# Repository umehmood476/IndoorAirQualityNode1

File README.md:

# IndoorAirQualityNode1
Indoor Air Quality Node 1

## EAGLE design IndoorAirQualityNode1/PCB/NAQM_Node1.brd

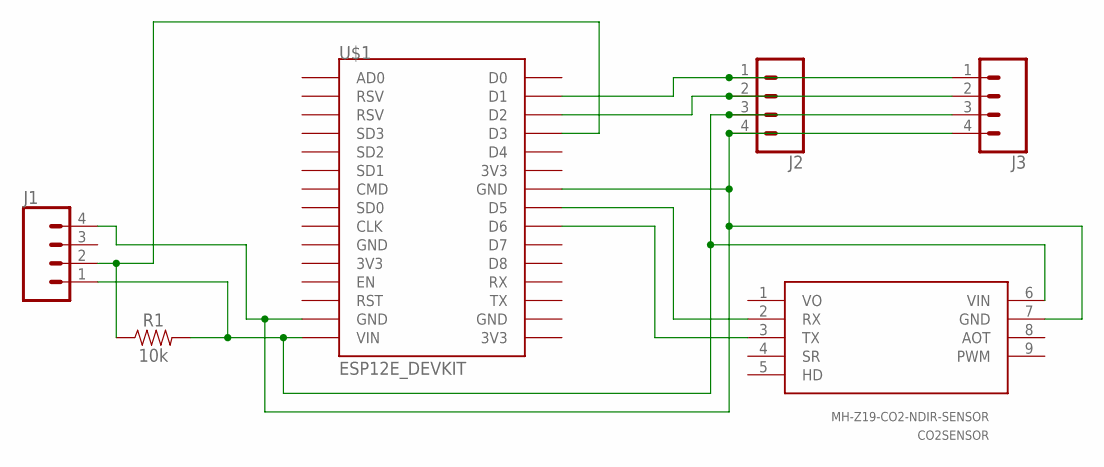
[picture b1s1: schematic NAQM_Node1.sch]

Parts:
CO2SENSOR: MH-Z19-CO2-NDIR-SENSOR; MH-Z19
J1, J2, J3: CONN_04PTH; 1X04
R1: 10k; AXIAL-0.3
U$1: ESP12E_DEVKIT

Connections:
unnamed: J2.1, J3.1, U$1.D1
unnamed: J2.2, J3.2, U$1.D2
unnamed: CO2SENSOR.6 (VIN), J1.1, J2.3, J3.3, R1.P$2 (2), U$1.VIN
unnamed: J1.2, R1.P$1 (1), U$1.D3
unnamed: CO2SENSOR.2 (RX), U$1.D5
unnamed: CO2SENSOR.3 (TX), U$1.D6
unnamed: CO2SENSOR.7 (GND), J1.4, J2.4, J3.4, U$1.GND@1 (GND), U$1.GND@2 (GND)
VO: CO2SENSOR.1 (VO)

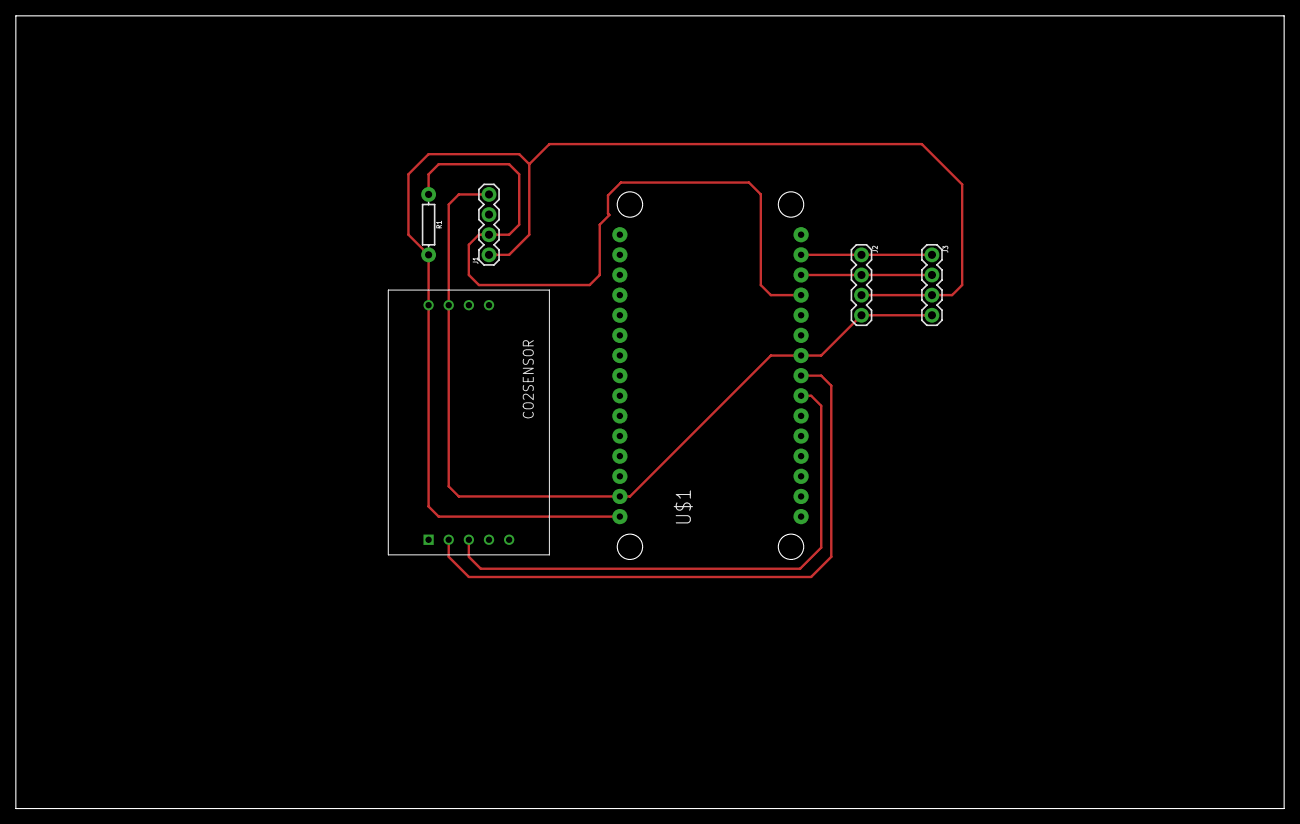
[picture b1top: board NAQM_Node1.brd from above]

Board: 2 copper layers, 160.0 x 100.0 mm, 6 parts (0 on the bottom side), 7 nets.

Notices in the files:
parts and their libraries:
SparkFun-Connectors: Licensing: Creative Commons ShareAlike 4.0 International - https://creativecommons.org/licenses/by-sa/4.0
